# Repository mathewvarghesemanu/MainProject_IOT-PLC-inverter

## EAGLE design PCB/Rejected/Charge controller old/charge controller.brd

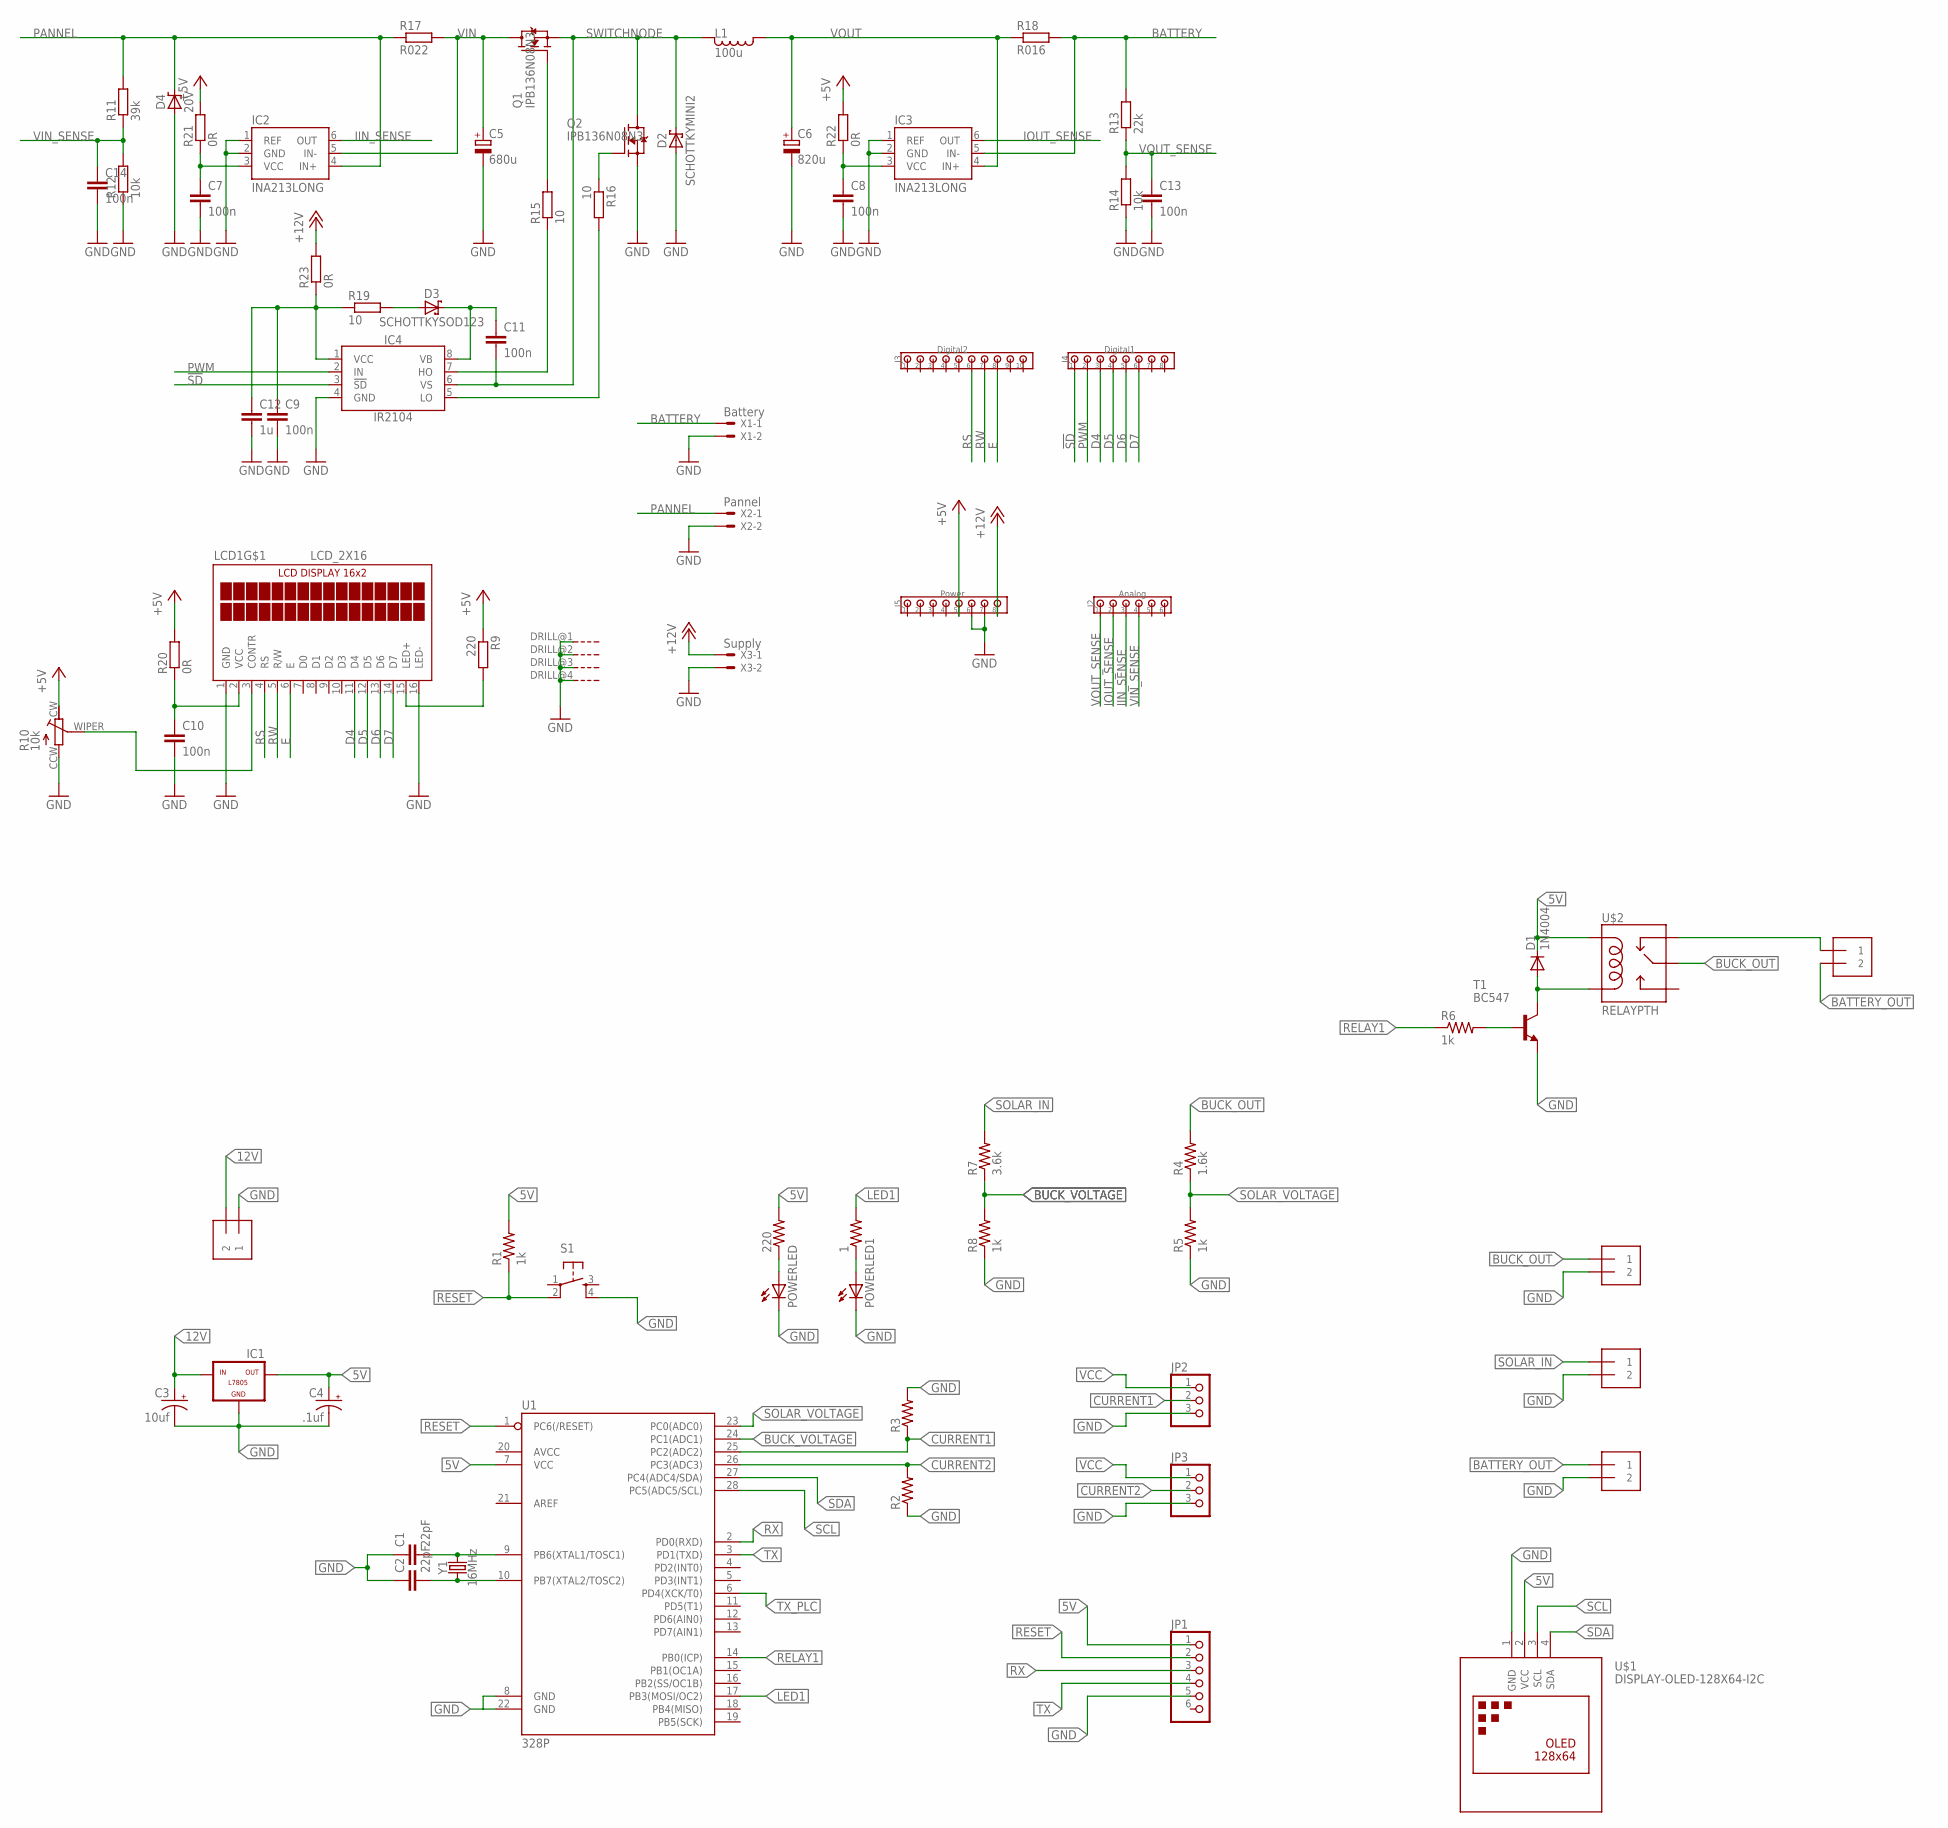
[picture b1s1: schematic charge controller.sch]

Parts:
1, 220: R-US_0204/5; 0204/5
BATTERY-OUT: 1X2-3.5MM
BAT_OUT: 1X2-3.5MM
BUCK-OUT: 1X2-3.5MM
C1, C2: 22pF; CAP-PTH-2.54
C3: 10uf; E5-5
C4: .1uf; E5-5
C5: 680u; 10MM
C6: 820u; 10MM
C7, C8, C9, C10, C11, C13, C14: 100n; C0805
C12: 1u; C0805
D1: 1N4004; DO41-10
D2: SCHOTTKYMINI2; MINI2-F3-B
D3: SCHOTTKYSOD123; SOD123
D4: 20V; SMC
IC1: L7805; 78XXL
IC2, IC3: INA213LONG; SC70-6_LONG
IC4: IR2104; SOIC8
J1: 1X2-3.5MM
J2: Analog; 100MIL_6X_ROUND
J3: Digital2; 100MIL_10X_ROUND
J4: Digital1; 100MIL_8X_ROUND
J5: Power; 100MIL_8X_ROUND
JP1: PINHD-1X6; 1X06
JP2, JP3: PINHD-1X3; 1X03
L1: 100u; MSS1583
LCD1: LCD_2X16
POWERLED, POWERLED1: LED5MM
Q1: IPB136N08N3; TO263-3
Q2: IPB136N08N3; TO263-3@1
R1, R5, R6, R8: 1k; 0204/5
R2, R3: R-US_0204/5; 0204/5
R4: 1.6k; 0204/5
R7: 3.6k; 0204/5
R9: 220; R0805
R10: 10k; RTRIM3314G
R11: 39k; R0805
R12, R14: 10k; R0805
R13: 22k; R0805
R15, R16, R19: 10; R0805
R17: R022; 0612
R18: R016; 0612
R20, R21, R22, R23: 0R; R0805
S1: TAC_SWITCHPTH; TACTILE-PTH
SOLAR-IN: 1X2-3.5MM
T1: BC547; TO92
U1: 328P; DIP28
U$1: DISPLAY-OLED-128X64-I2C
U$2: RELAYPTH; SRD-05VDC-SL-C
X1: Battery; 200MIL_2X
X2: Pannel; 200MIL_2X
X3: Supply; 22-23-2021
Y1: 16MHz; HC49US

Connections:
5V: 220.2, C4.+, D1.C, IC1.OUT, JP1.1, R1.2, U1.7 (VCC), U$1.2 (VCC), U$2.COIL1
12V: C3.+, IC1.IN, J1.2
!SD!: IC4.3 (!SD!), J4.1
+5V: J5.5, R9.1, R10.CW, R20.2, R21.2, R22.2
+12V: J5.8, R23.2, X3.1
BATTERY: IC3.5 (IN-), R13.2, R18.2, X1.1
BATTERY_OUT: BATTERY-OUT.1, BAT_OUT.2
BUCK_OUT: BUCK-OUT.1, R4.2, U$2.SWCOMMON
BUCK_VOLTAGE: R7.1, R8.2, U1.24 (PC1(ADC1))
CURRENT1: JP2.2, R3.1, U1.25 (PC2(ADC2))
CURRENT2: JP3.2, R2.2, U1.26 (PC3(ADC3))
D4: J4.3, LCD1.11 (D4)
D5: J4.4, LCD1.12 (D5)
D6: J4.5, LCD1.13 (D6)
D7: J4.6, LCD1.14 (D7)
E: J3.8, LCD1.6 (E)
GND: BATTERY-OUT.2, BUCK-OUT.2, C1.1, C2.1, C3.-, C4.-, C5.-, C6.-, C7.2, C8.2, C9.2, C10.2, C12.2, C13.2, C14.2, D2.A, D4.A, IC1.GND, IC2.1 (REF), IC2.2 (GND), IC3.1 (REF), IC3.2 (GND), IC4.4 (GND), J1.1, J5.6, J5.7, JP1.5, JP2.3, JP3.3, LCD1.1 (GND), LCD1.16 (LED-), LCD1.DRILL@1 (G), LCD1.DRILL@2 (G), LCD1.DRILL@3 (G), LCD1.DRILL@4 (G), POWERLED.K (C), POWERLED1.K (C), Q2.3 (S), R2.1, R3.2, R5.1, R8.1, R10.CCW, R12.1, R14.1, S1.4, SOLAR-IN.2, T1.1 (E), U1.8 (GND), U1.22 (GND), U$1.1 (GND), X1.2, X2.2, X3.2
IIN_SENSE: IC2.6 (OUT), J2.3
IOUT_SENSE: IC3.6 (OUT), J2.2
LED1: 1.2, U1.17 (PB3(MOSI/OC2))
unnamed: 220.1, POWERLED.A
unnamed: C1.2, U1.9 (PB6(XTAL1/TOSC1)), Y1.2
unnamed: C2.2, U1.10 (PB7(XTAL2/TOSC2)), Y1.1
unnamed: LCD1.15 (LED+), R9.2
unnamed: 1.1, POWERLED1.A
unnamed: R6.2, T1.2 (B)
unnamed: D1.A, T1.3 (C), U$2.COIL0
unnamed: Q1.1 (G), R15.2
unnamed: BAT_OUT.1, U$2.SWCLOSED (SWCLOSE)
unnamed: LCD1.3 (CONTR), R10.WIPER
unnamed: Q2.1 (G), R16.1
unnamed: D3.A, R19.2
unnamed: C11.1, D3.C, IC4.8 (VB)
unnamed: IC4.7 (HO), R15.1
unnamed: IC4.5 (LO), R16.2
unnamed: C10.1, LCD1.2 (VCC), R20.1
unnamed: C7.1, IC2.3 (VCC), R21.1
unnamed: C8.1, IC3.3 (VCC), R22.1
unnamed: C9.1, C12.1, IC4.1 (VCC), R19.1, R23.1
PANNEL: D4.C, IC2.4 (IN+), R11.2, R17.1, X2.1
PWM: IC4.2 (IN), J4.2
RELAY1: R6.1, U1.14 (PB0(ICP))
RESET: JP1.2, R1.1, S1.2, U1.1 (PC6(/RESET))
RS: J3.6, LCD1.4 (RS)
RW: J3.7, LCD1.5 (R/W)
RX: JP1.3, U1.2 (PD0(RXD))
SCL: U1.28 (PC5(ADC5/SCL)), U$1.3 (SCL)
SDA: U1.27 (PC4(ADC4/SDA)), U$1.4 (SDA)
SOLAR_IN: R7.2, SOLAR-IN.1
SOLAR_VOLTAGE: R4.1, R5.2, U1.23 (PC0(ADC0))
SWITCHNODE: C11.2, D2.C, IC4.6 (VS), L1.2, Q1.3 (S), Q2.TAB (D)
TX: JP1.4, U1.3 (PD1(TXD))
TX_PLC: U1.6 (PD4(XCK/T0))
VCC: JP2.1, JP3.1
VIN: C5.+, IC2.5 (IN-), Q1.TAB (D), R17.2
VIN_SENSE: C14.1, J2.4, R11.1, R12.2
VOUT: C6.+, IC3.4 (IN+), L1.1, R18.1
VOUT_SENSE: C13.1, J2.1, R13.1, R14.2

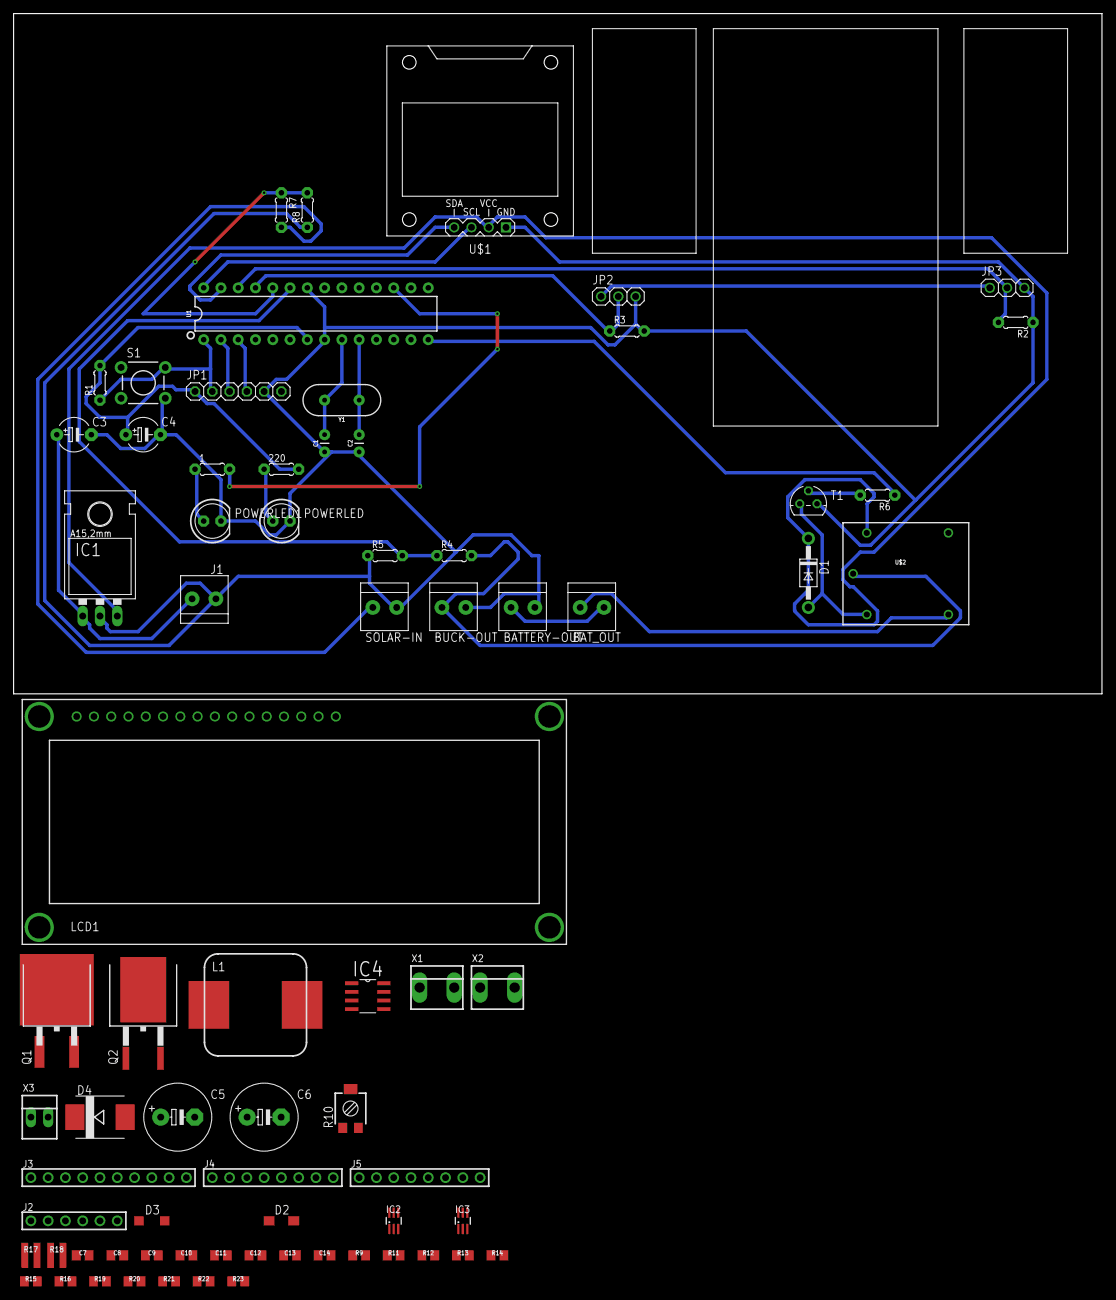
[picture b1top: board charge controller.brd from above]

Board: 2 copper layers, 160.0 x 100.0 mm, 74 parts (0 on the bottom side), 57 nets.

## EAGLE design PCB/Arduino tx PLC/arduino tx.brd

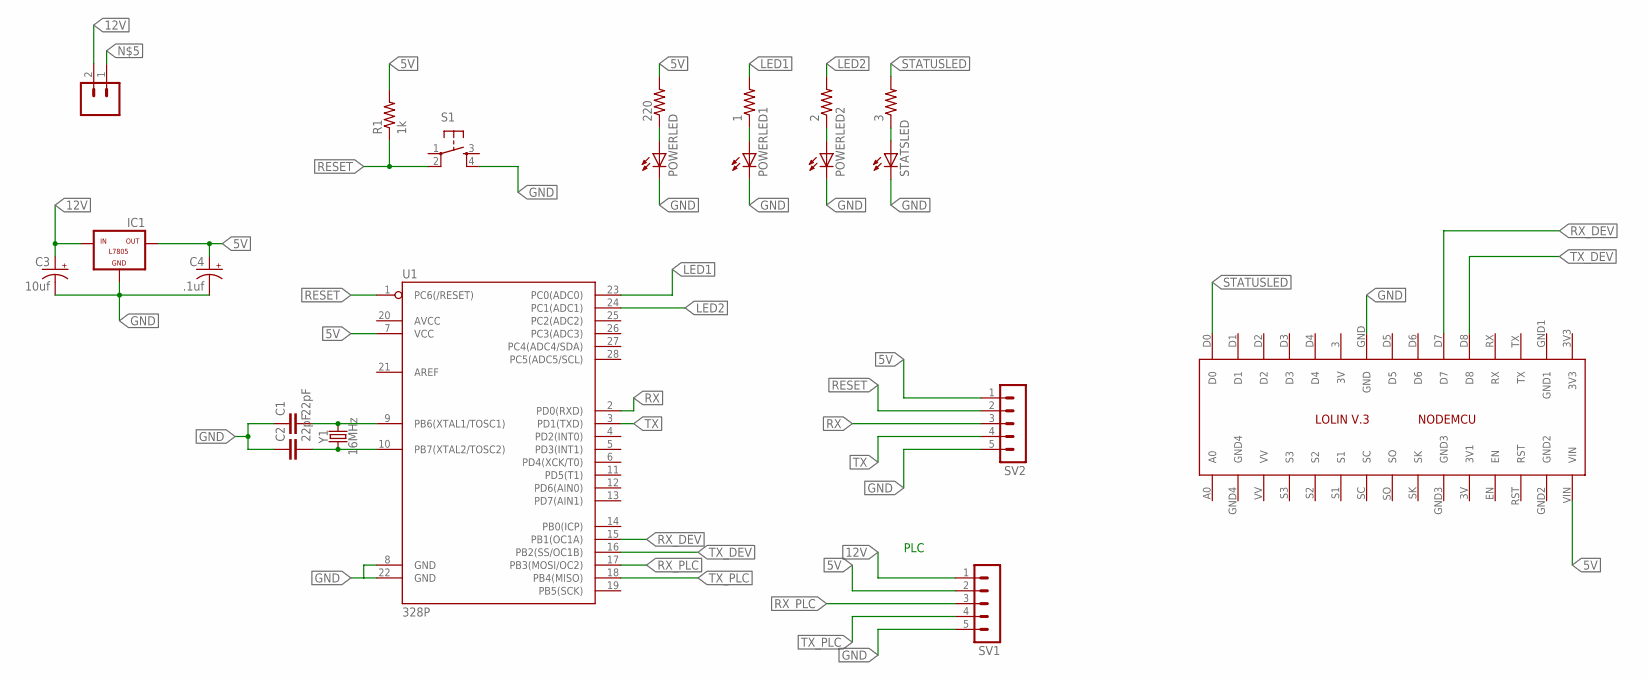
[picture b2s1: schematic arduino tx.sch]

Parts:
1, 2, 3, 220: R-US_0204/5; 0204/5
C1, C2: 22pF; CAP-PTH-2.54
C3: 10uf; E5-5
C4: .1uf; E5-5
IC1: L7805; 78XXL
IC2: NODEMCU_LOLINV3
J1: CONN_025MM; SCREWTERMINAL-5MM-2
POWERLED, POWERLED1, POWERLED2: LED5MM
R1: 1k; 0204/5
S1: TAC_SWITCHPTH; TACTILE-PTH
STATSLED: LED5MM
SV1, SV2: MA05-1
U1: 328P; DIP28
Y1: 16MHz; HC49US

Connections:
5V: 220.2, C4.+, IC1.OUT, IC2.VIN, R1.2, SV1.2, SV2.1, U1.7 (VCC)
12V: C3.+, IC1.IN, J1.2, SV1.1
GND: C1.1, C2.1, C3.-, C4.-, IC1.GND, IC2.GND, POWERLED.K (C), POWERLED1.K (C), POWERLED2.K (C), S1.4, STATSLED.K (C), SV1.5, SV2.5, U1.8 (GND), U1.22 (GND)
LED1: 1.2, U1.23 (PC0(ADC0))
LED2: 2.2, U1.24 (PC1(ADC1))
unnamed: 220.1, POWERLED.A
unnamed: C1.2, U1.9 (PB6(XTAL1/TOSC1)), Y1.2
unnamed: C2.2, U1.10 (PB7(XTAL2/TOSC2)), Y1.1
unnamed: 1.1, POWERLED1.A
unnamed: 2.1, POWERLED2.A
unnamed: 3.1, STATSLED.A
RESET: R1.1, S1.2, SV2.2, U1.1 (PC6(/RESET))
RX: SV2.3, U1.2 (PD0(RXD))
RX_DEV: IC2.D7, U1.15 (PB1(OC1A))
RX_PLC: SV1.3, U1.17 (PB3(MOSI/OC2))
STATUSLED: 3.2, IC2.D0
TX: SV2.4, U1.3 (PD1(TXD))
TX_DEV: IC2.D8, U1.16 (PB2(SS/OC1B))
TX_PLC: SV1.4, U1.18 (PB4(MISO))

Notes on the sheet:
PLC

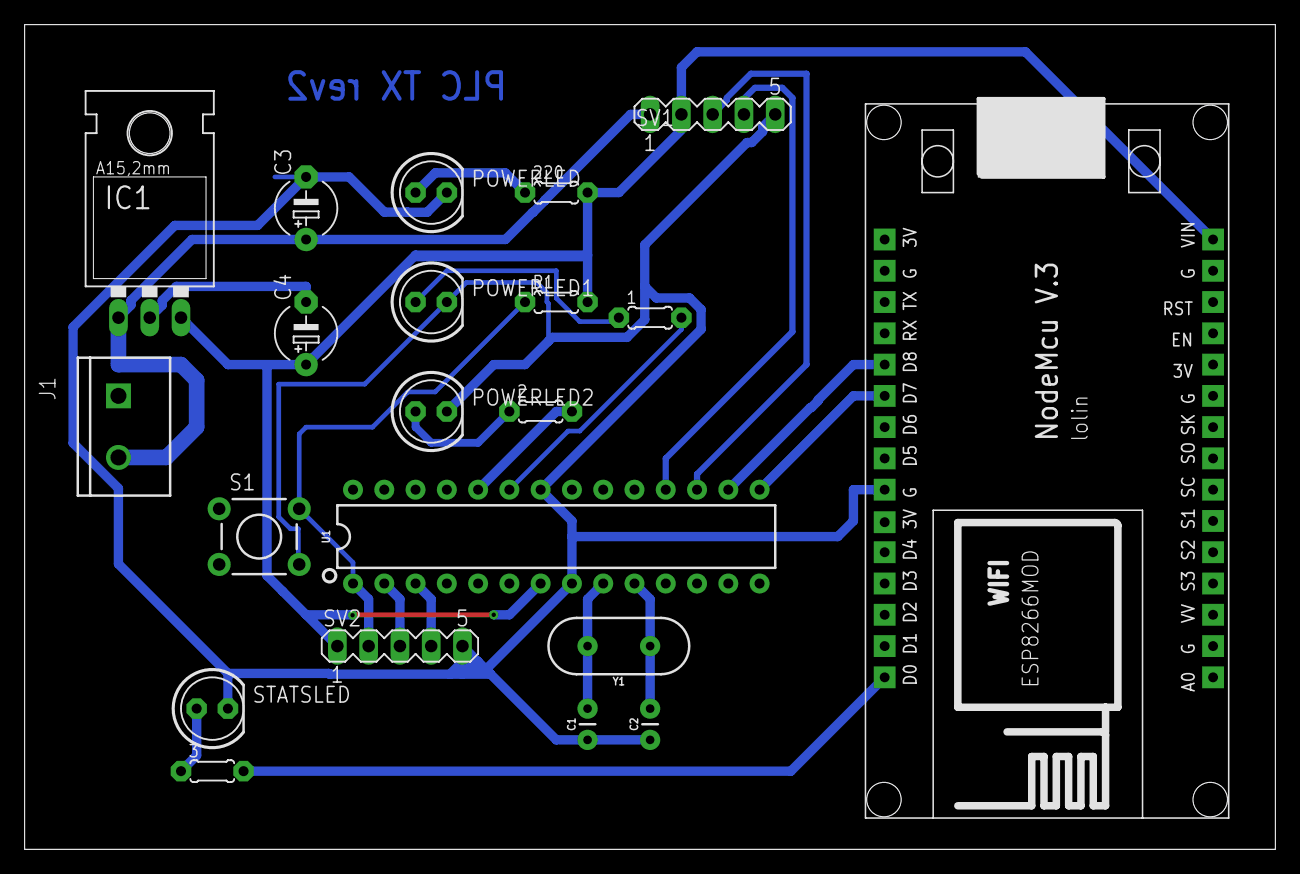
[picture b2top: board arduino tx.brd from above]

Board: 2 copper layers, 101.6 x 67.0 mm, 21 parts (0 on the bottom side), 19 nets.

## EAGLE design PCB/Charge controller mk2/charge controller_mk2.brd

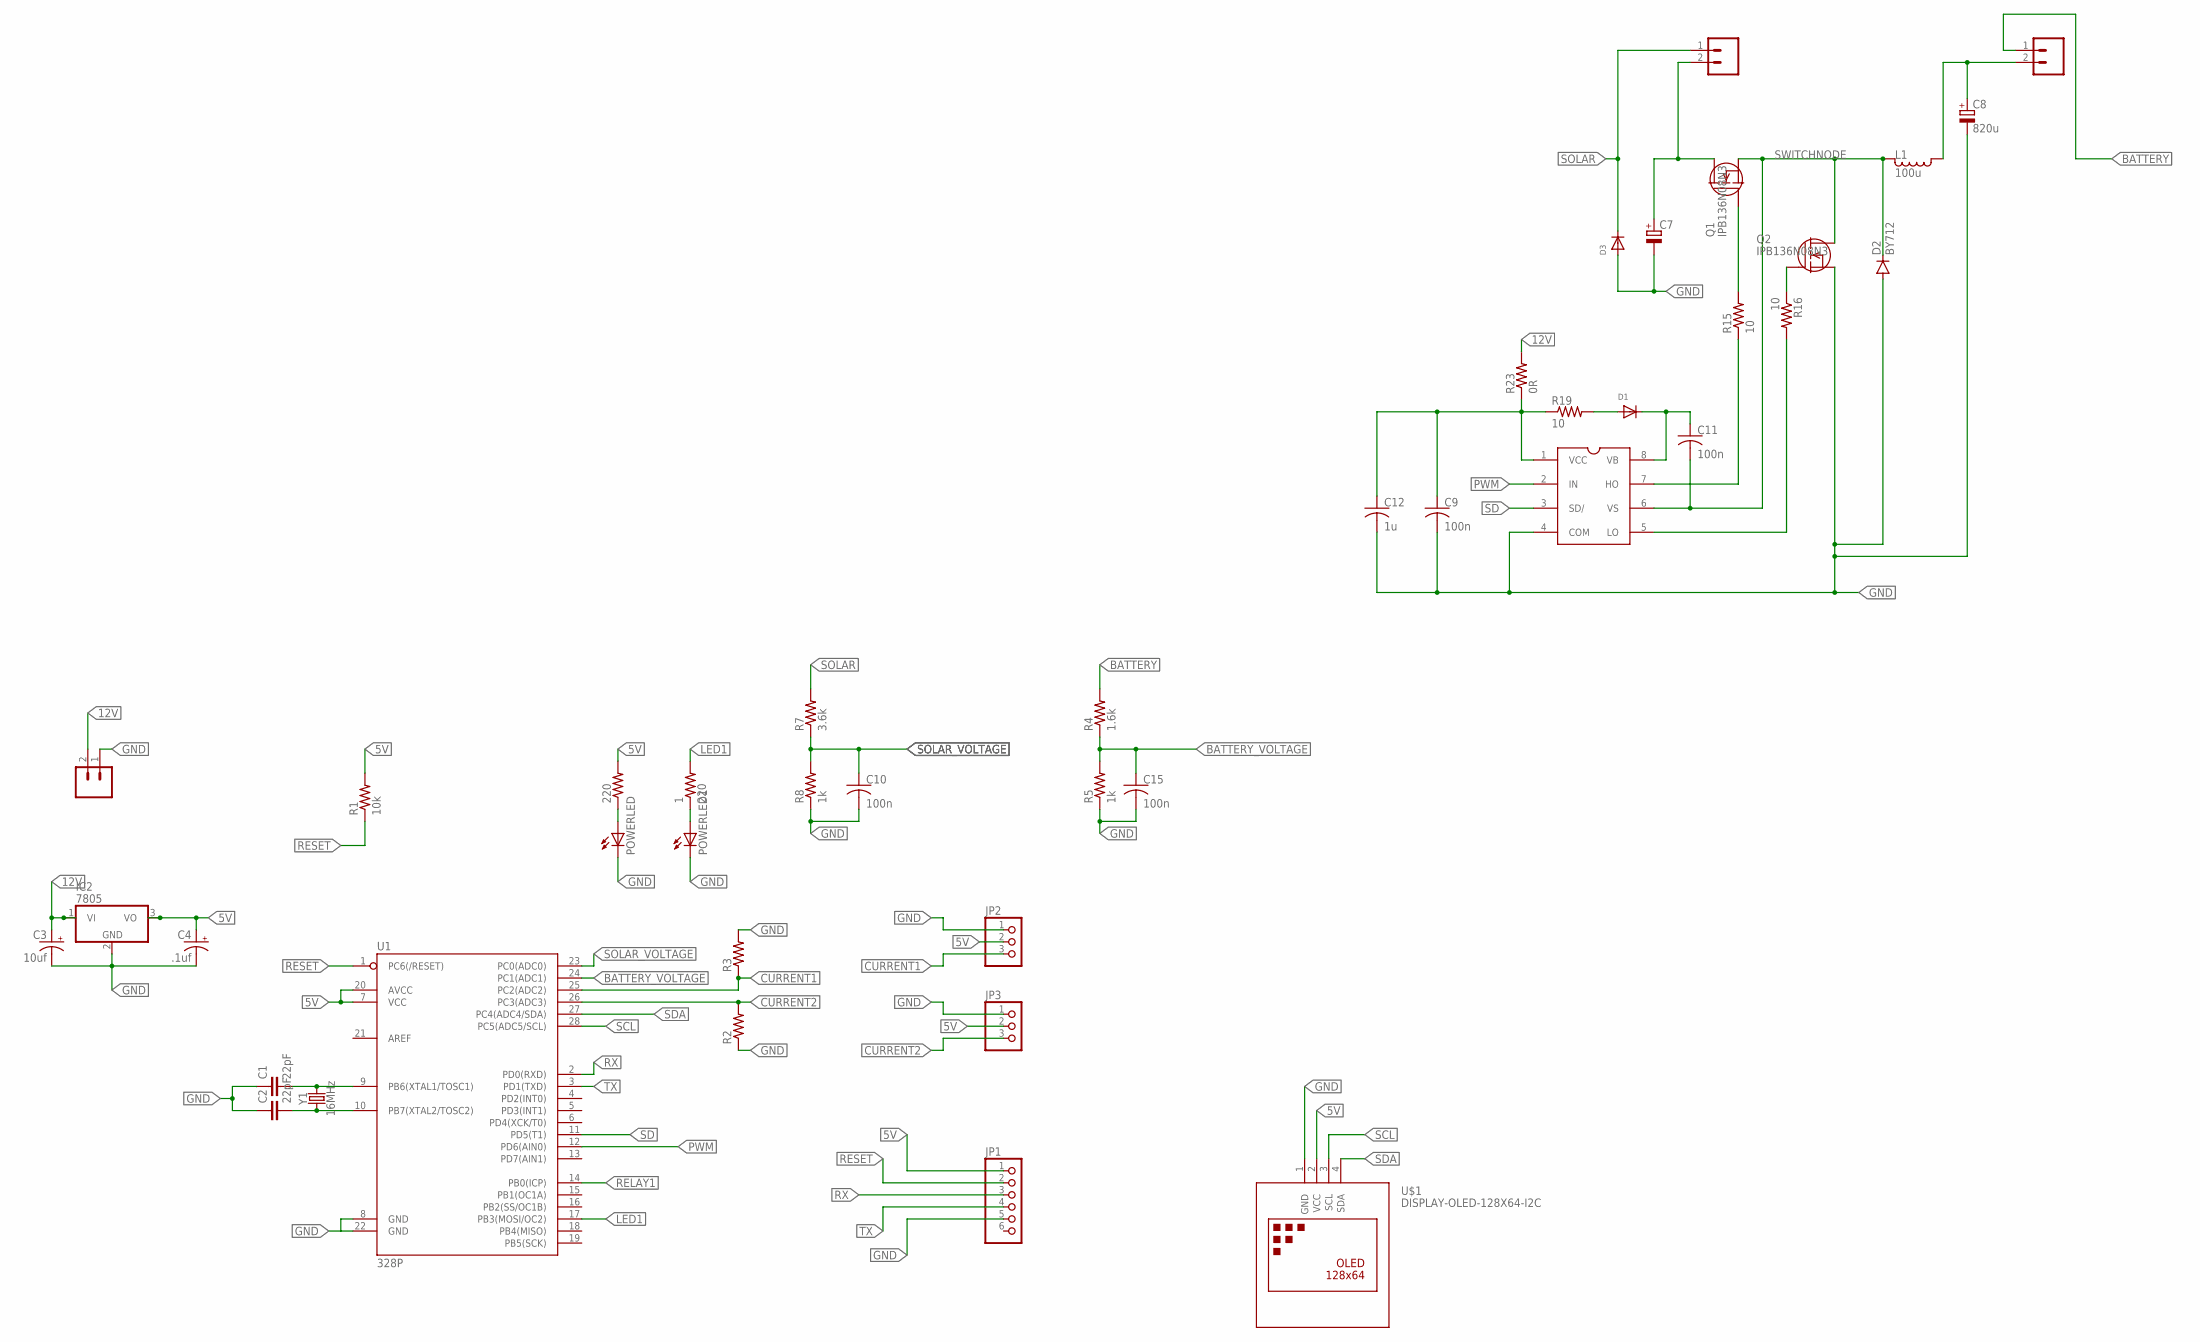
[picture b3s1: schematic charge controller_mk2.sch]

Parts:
1: 220; 0204/5
220: R-US_0204/5; 0204/5
BATTERY-OUT: CONN_025MM; SCREWTERMINAL-5MM-2
C1, C2: 22pF; CAP-PTH-2.54
C3: 10uf; E5-5
C4: .1uf; E5-5
C7: 680u; 10MM
C8: 820u; 10MM
C9, C10, C15: 100n; C050-025X075
C11: 100n; C050-055X075
C12: 1u; C050-025X075
D1, D3: DIODEDO-1N4148; DO-1N4148
D2: BY712; SOD61E
IC2: 7805; TO220V
J1: PWR_in; SCREWTERMINAL-5MM-2
JP1: PINHD-1X6; 1X06
JP2, JP3: PINHD-1X3; 1X03
L1: 100u; MSS1583
POWERLED, POWERLED1: LED5MM
Q1, Q2: IPB136N08N3; TO220
R1: 10k; 0204/5
R2, R3: R-US_0207/7; 0207/7
R4: 1.6k; 0207/7
R5, R8: 1k; 0207/7
R7: 3.6k; 0207/7
R15, R16, R19: 10; 0204/7
R23: 0R; 0204/7
SOLAR-IN: CONN_025MM; SCREWTERMINAL-5MM-2
U1: 328P; DIP28
U$1: DISPLAY-OLED-128X64-I2C
U$2: IR2104
Y1: 16MHz; HC49US

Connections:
5V: 220.2, C4.+, IC2.3 (VO), JP1.1, JP2.2, JP3.2, R1.2, U1.7 (VCC), U1.20 (AVCC), U$1.2 (VCC)
12V: C3.+, IC2.1 (VI), J1.2, R23.2
BATTERY: BATTERY-OUT.1, R4.2
BATTERY_VOLTAGE: C15.1, R4.1, R5.2, U1.24 (PC1(ADC1))
CURRENT1: JP2.3, R3.1, U1.25 (PC2(ADC2))
CURRENT2: JP3.3, R2.2, U1.26 (PC3(ADC3))
GND: C1.1, C2.1, C3.-, C4.-, C7.-, C8.-, C9.2, C10.2, C12.2, C15.2, D2.A, D3.A, IC2.2 (GND), J1.1, JP1.5, JP2.1, JP3.1, POWERLED.K (C), POWERLED1.K (C), Q2.3 (S), R2.1, R3.2, R5.1, R8.1, U1.8 (GND), U1.22 (GND), U$1.1 (GND), U$2.4 (COM)
LED1: 1.2, U1.17 (PB3(MOSI/OC2))
unnamed: 220.1, POWERLED.A
unnamed: C1.2, U1.9 (PB6(XTAL1/TOSC1)), Y1.2
unnamed: C2.2, U1.10 (PB7(XTAL2/TOSC2)), Y1.1
unnamed: D1.A, R19.2
unnamed: 1.1, POWERLED1.A
unnamed: BATTERY-OUT.2, C8.+, L1.1
unnamed: Q1.1 (G), R15.2
unnamed: C7.+, Q1.2 (D), SOLAR-IN.2
unnamed: Q2.1 (G), R16.1
unnamed: C11.1, D1.C, U$2.8 (VB)
unnamed: R15.1, U$2.7 (HO)
unnamed: R16.2, U$2.5 (LO)
unnamed: C9.1, C12.1, R19.1, R23.1, U$2.1 (VCC)
PWM: U1.12 (PD6(AIN0)), U$2.2 (IN)
RELAY1: U1.14 (PB0(ICP))
RESET: JP1.2, R1.1, U1.1 (PC6(/RESET))
RX: JP1.3, U1.2 (PD0(RXD))
SCL: U1.28 (PC5(ADC5/SCL)), U$1.3 (SCL)
SD: U1.11 (PD5(T1)), U$2.3 (SD/)
SDA: U1.27 (PC4(ADC4/SDA)), U$1.4 (SDA)
SOLAR: D3.C, R7.2, SOLAR-IN.1
SOLAR_VOLTAGE: C10.1, R7.1, R8.2, U1.23 (PC0(ADC0))
SWITCHNODE: C11.2, D2.C, L1.2, Q1.3 (S), Q2.2 (D), U$2.6 (VS)
TX: JP1.4, U1.3 (PD1(TXD))

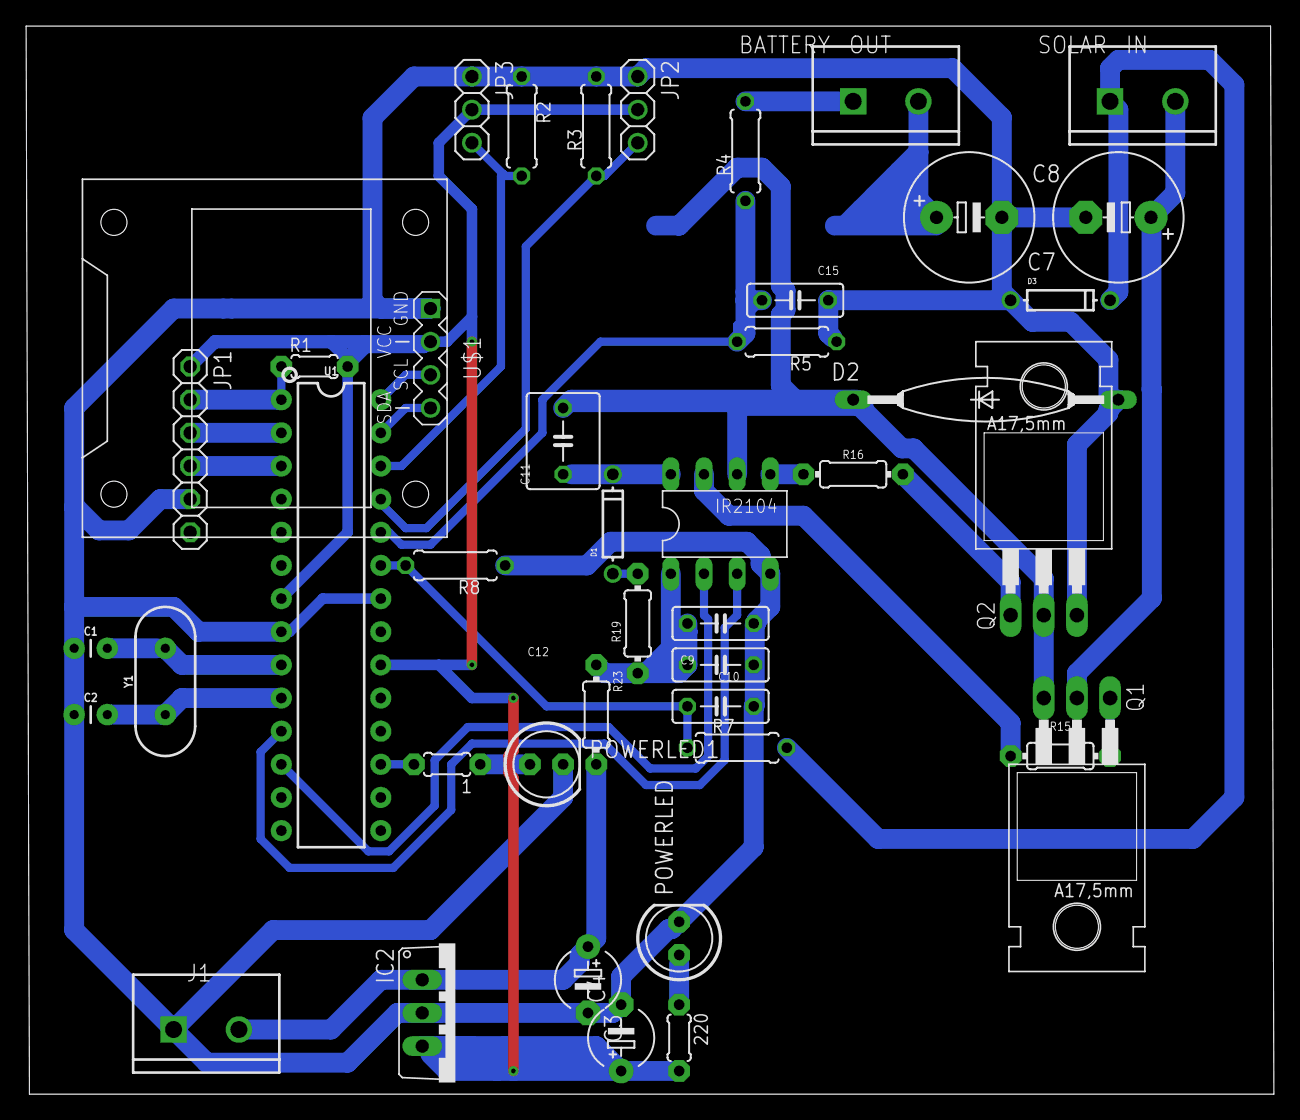
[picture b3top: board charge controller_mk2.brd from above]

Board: 2 copper layers, 95.6 x 81.8 mm, 43 parts (1 on the bottom side), 31 nets.

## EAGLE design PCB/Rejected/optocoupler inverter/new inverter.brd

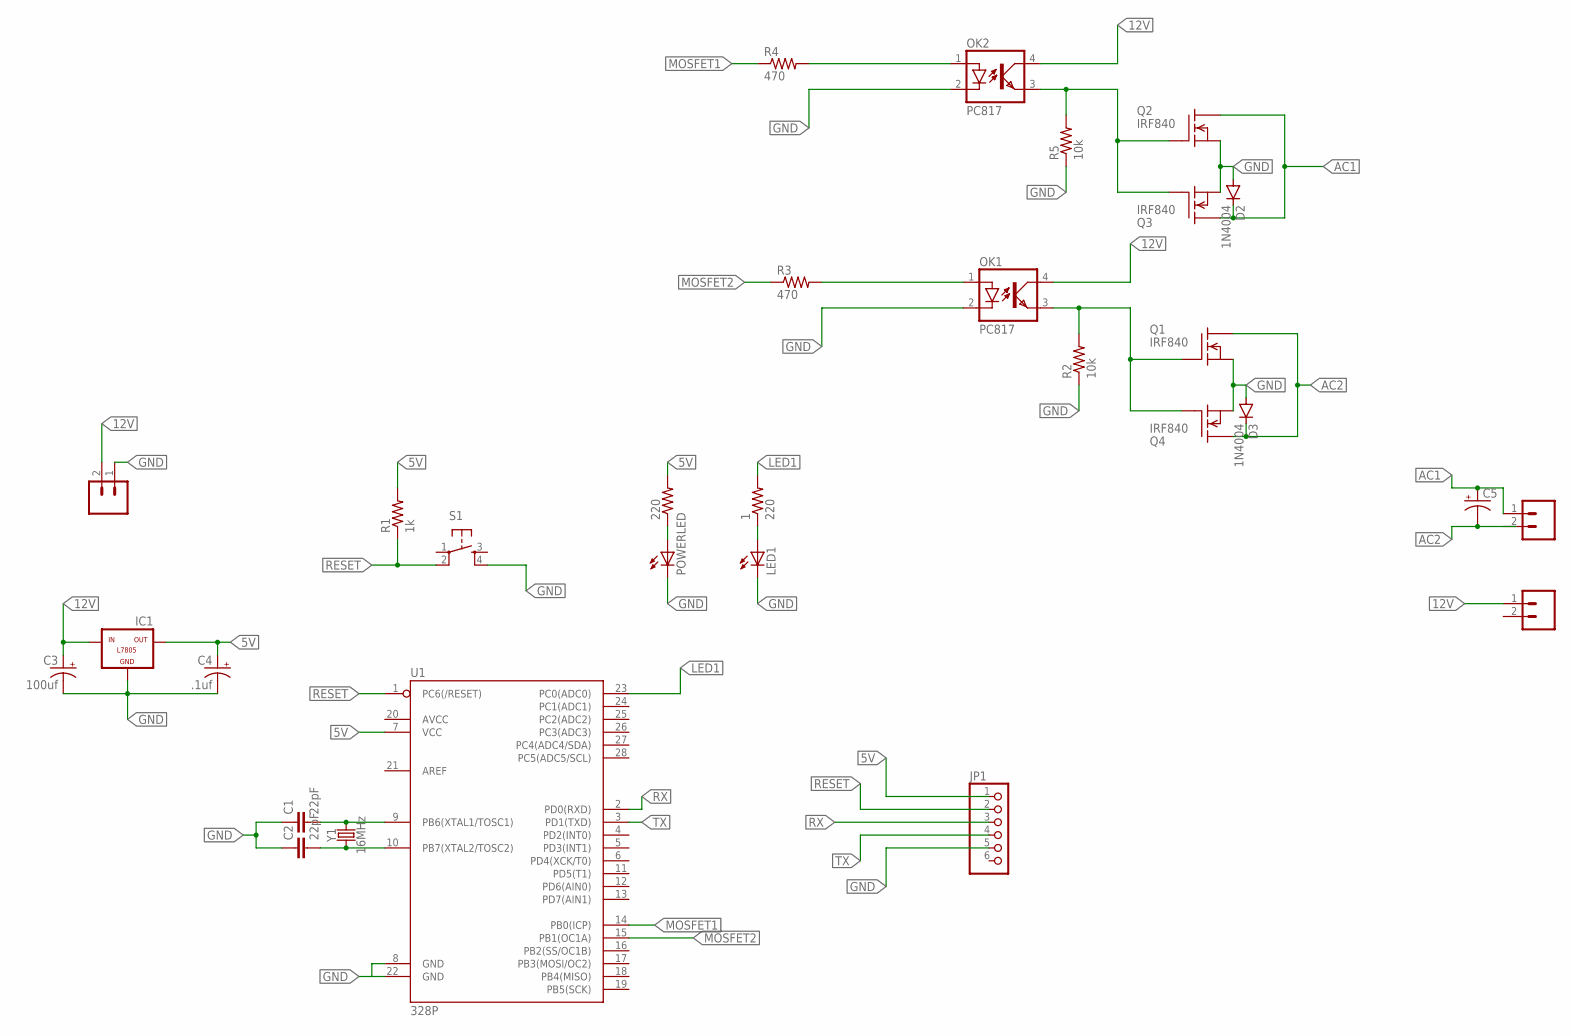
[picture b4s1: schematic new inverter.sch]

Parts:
1: 220; 0204/5
220: R-US_0204/5; 0204/5
C1, C2: 22pF; CAP-PTH-2.54
C3: 100uf; E5-5
C4: .1uf; E5-5
C5: CPOL-USE5-13; E5-13
D2, D3: 1N4004; DO41-10
IC1: L7805; 78XXL
J1, J2, J3: CONN_025MM; SCREWTERMINAL-5MM-2
JP1: PINHD-1X6; 1X06
LED1: LED5MM
OK1, OK2: PC817; DIL04
POWERLED: LED5MM
Q1, Q2, Q3, Q4: IRF840; TO220
R1: 1k; 0204/5
R2, R5: 10k; 0204/5
R3, R4: 470; 0204/5
S1: TAC_SWITCHPTH; TACTILE-PTH
U1: 328P; DIP28
Y1: 16MHz; HC49US

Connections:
5V: 220.2, C4.+, IC1.OUT, JP1.1, R1.2, U1.7 (VCC)
12V: C3.+, IC1.IN, J1.2, J2.1, OK1.4 (COL), OK2.4 (COL)
AC1: C5.+, D2.C, J3.1, Q2.2 (D), Q3.2 (D)
AC2: C5.-, D3.C, J3.2, Q1.2 (D), Q4.2 (D)
GND: C1.1, C2.1, C3.-, C4.-, D2.A, D3.A, IC1.GND, J1.1, JP1.5, LED1.K (C), OK1.2 (C), OK2.2 (C), POWERLED.K (C), Q1.3 (S), Q2.3 (S), Q3.3 (S), Q4.3 (S), R2.1, R5.1, S1.4, U1.8 (GND), U1.22 (GND)
LED1: 1.2, U1.23 (PC0(ADC0))
MOSFET1: R4.1, U1.14 (PB0(ICP))
MOSFET2: R3.1, U1.15 (PB1(OC1A))
unnamed: 220.1, POWERLED.A
unnamed: C1.2, U1.9 (PB6(XTAL1/TOSC1)), Y1.2
unnamed: C2.2, U1.10 (PB7(XTAL2/TOSC2)), Y1.1
unnamed: OK1.1 (A), R3.2
unnamed: OK1.3 (EMIT), Q1.1 (G), Q4.1 (G), R2.2
unnamed: OK2.3 (EMIT), Q2.1 (G), Q3.1 (G), R5.2
unnamed: OK2.1 (A), R4.2
unnamed: 1.1, LED1.A
RESET: JP1.2, R1.1, S1.2, U1.1 (PC6(/RESET))
RX: JP1.3, U1.2 (PD0(RXD))
TX: JP1.4, U1.3 (PD1(TXD))

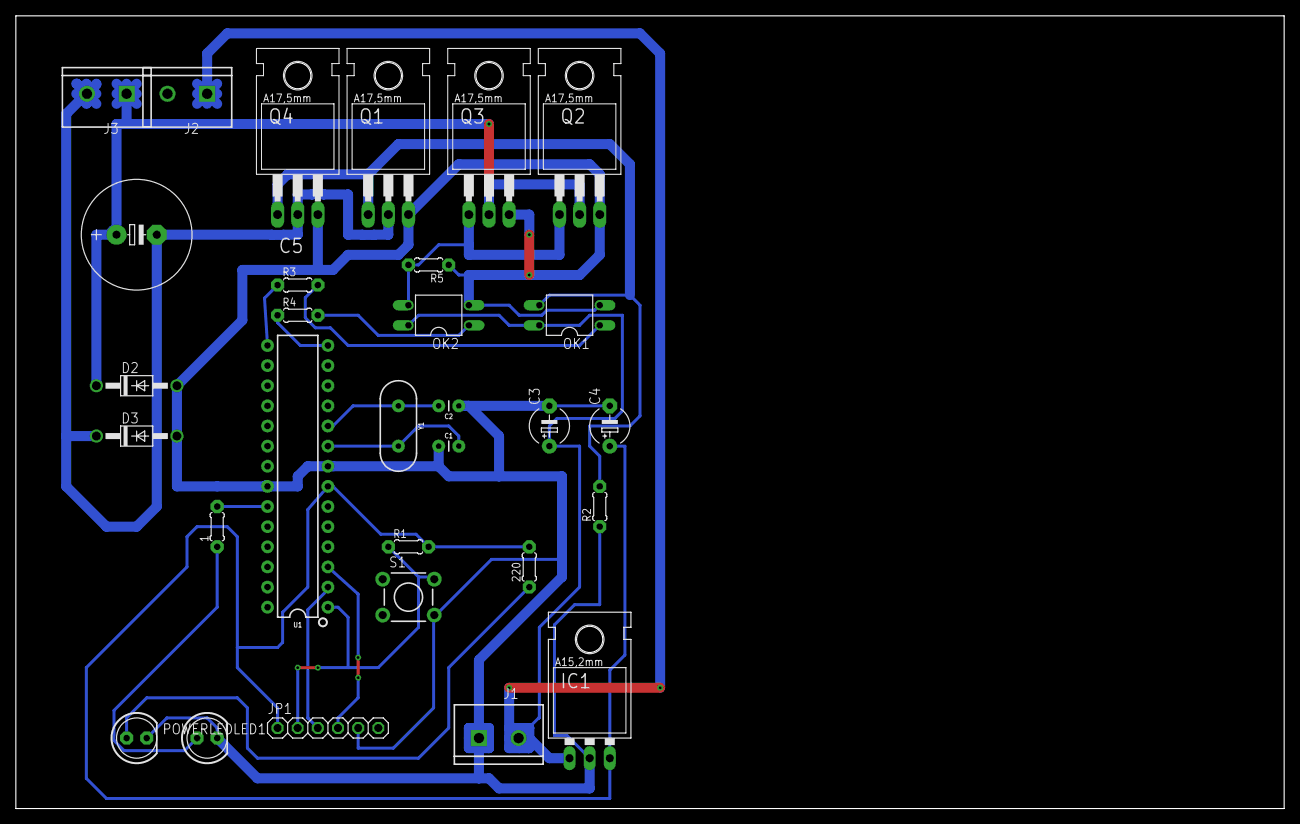
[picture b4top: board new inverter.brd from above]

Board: 2 copper layers, 160.0 x 100.0 mm, 30 parts (0 on the bottom side), 19 nets.

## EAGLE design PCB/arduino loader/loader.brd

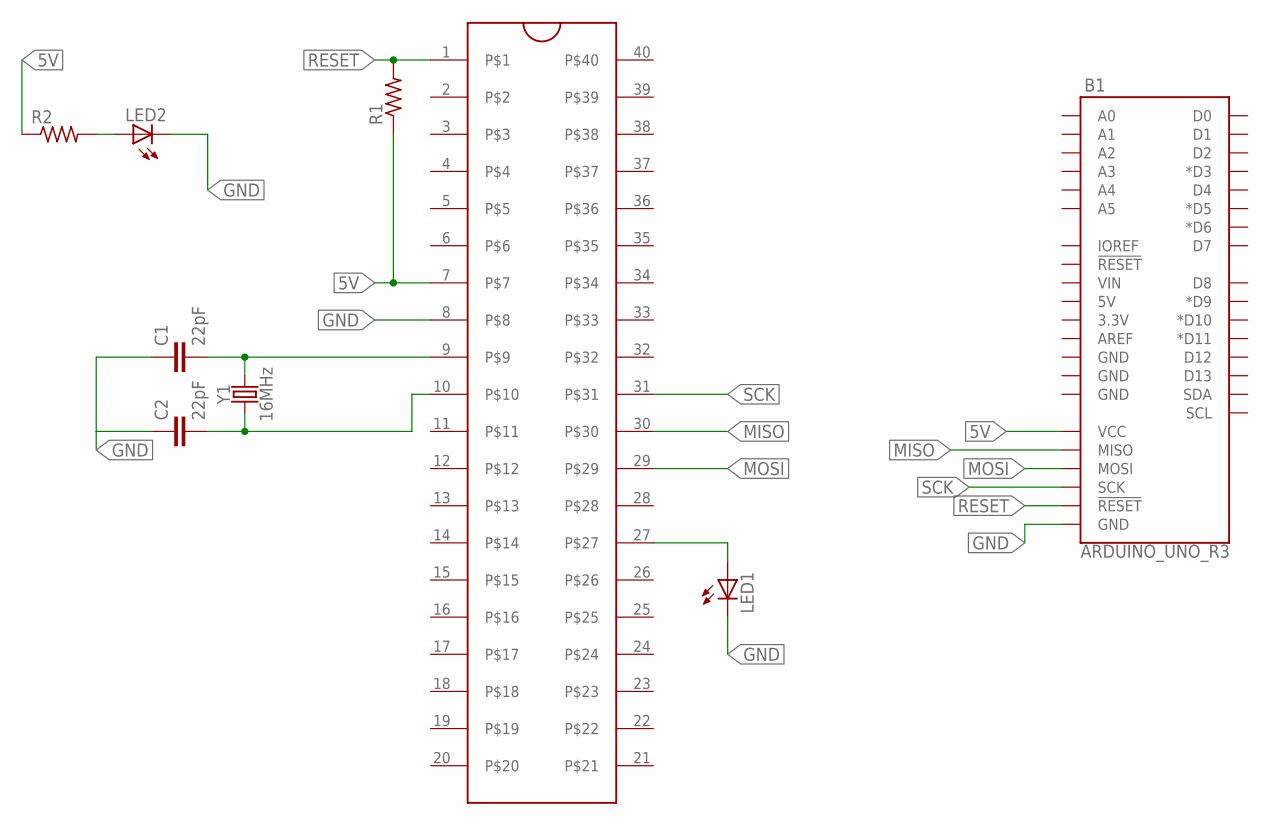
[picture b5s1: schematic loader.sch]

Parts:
B1: ARDUINO_UNO_R3; ARDUINO_R3
C1, C2: 22pF; CAP-PTH-2.54
LED1, LED2: LED5MM
R1, R2: R-US_0309/10; 0309/10
U$1: ZIFSOCKET-40-6DIL40-6-ZIF_SOCKET; DIL40-6-ZIF_SOCKET
Y1: 16MHz; HC49US

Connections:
5V: B1.VCC, R1.1, R2.1, U$1.7
GND: B1.GND@1 (GND), C1.1, C2.1, LED1.K (C), LED2.K (C), U$1.8
MISO: B1.MISO, U$1.30
MOSI: B1.MOSI, U$1.29
unnamed: C1.2, U$1.9, Y1.2
unnamed: C2.2, U$1.10, Y1.1
unnamed: LED1.A, U$1.27
unnamed: LED2.A, R2.2
RESET: B1.RESET@2 (!RESET!), R1.2, U$1.1
SCK: B1.SCK, U$1.31

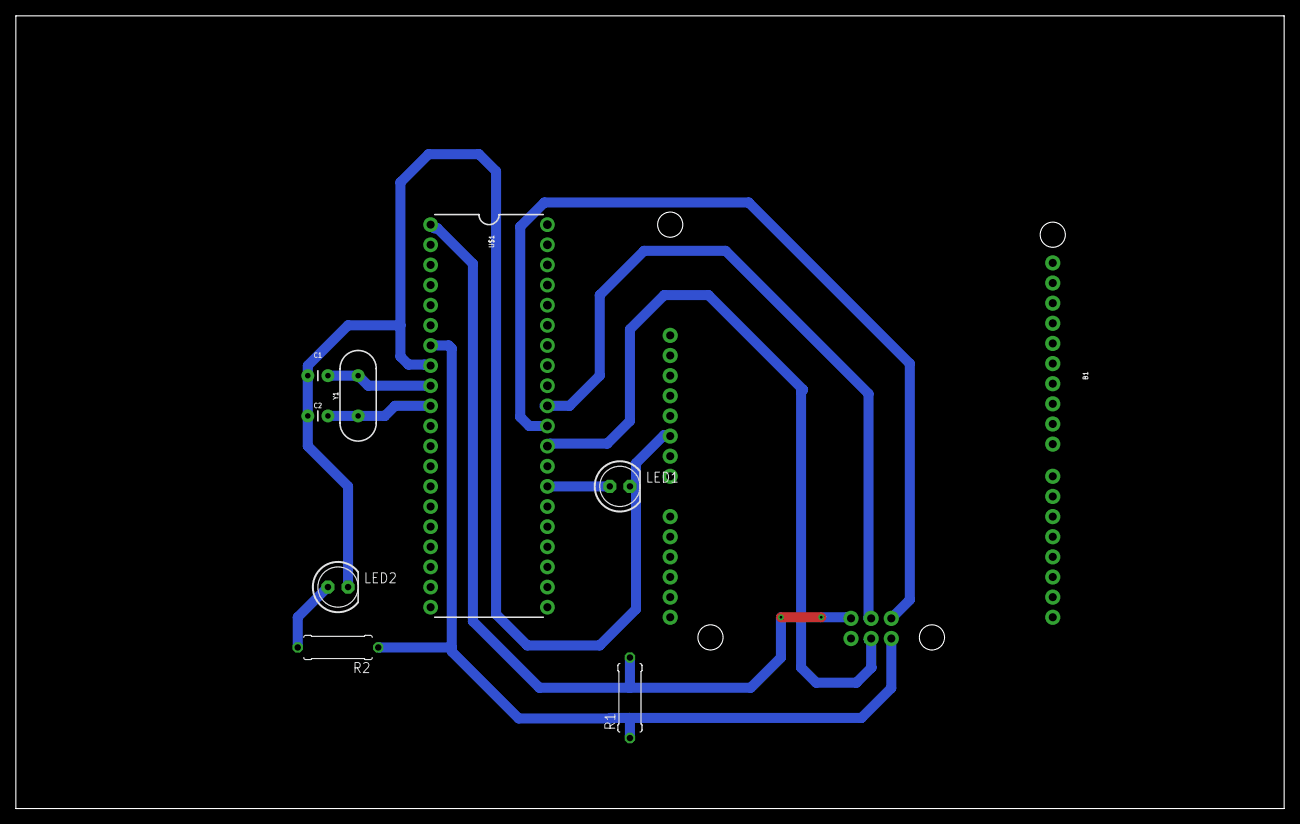
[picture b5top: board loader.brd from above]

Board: 2 copper layers, 160.0 x 100.0 mm, 9 parts (0 on the bottom side), 10 nets.

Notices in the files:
parts and their libraries:
SparkFun-Capacitors: Licensing: Creative Commons ShareAlike 4.0 International - https://creativecommons.org/licenses/by-sa/4.0
diy-modules: Released under the Creative Commons Attribution 4.0 International License: http://creativecommons.org/licenses/by/4.0
